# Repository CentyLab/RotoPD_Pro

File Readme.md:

## RotoPD Pro - USB-C PD 3.1 Breakout I2C 240W

## Related Links
- [AP33772S Arduino - GitHub](https://github.com/CentyLab/AP33772S-CentyLab)
- [INA238 Arduino - GitHub](https://github.com/RobTillaart/INA238)
- [RotoPD Pro Project - Hackaday](https://hackaday.io/project/204943-rotopd-pro-usb-c-240w-breakout-i2c)

You can install the libraries directly on ArduinoIDE. Library version 1.1.0 and later will support RotoPD Pro

## Description

While traditional power adapters can provide a variety of current but fixed to 5V output, our RotoPD Pro leverages advanced power delivery protocols to achieve a versatile output range — 4.5V to 48V at 240W max. The breakout board use a stand alone Power Delivery Sink controller to negotiate with your modern charger and provide different output voltage.

Centylab's RotoPD Pro can unlock more advance mode in your USB-C power supplies like Programmable Power Supply (PPS) and Adjustable Voltage Supply (AVS), to provide even more granular voltage adjustment. The RotoPD Pro simplifies power negotiation with USB-C adapters, handling the complex process of establishing power delivery contracts. The controller does all the heavy lifting of power negotiation and provides an easy way to configure over I2C, free your micro-controller from the complicated USB-C PD protocol.

To config the board, you will need an I2C bus. The board integrates seamlessly into the Qwiic and STEMMA QT ecosystems, no soldering is required. Unlike the previous version, the board only work with **3.3V I2C logic voltage.**

To make it even easier to use, RotoPD Pro includes a built-in buck converter that efficiently steps down USB-C VBUS power to a stable 5V output, making it perfect for powering microcontrollers, sensors, and other low-voltage components in your project.

## Requirements for AVS
To ultilize AVS power profile, you will need a powerbank or charger that has AVS profile and a 240W USB-C cable. Here are some chargers that we found support AVS profile.

+ [Framework 180W](https://frame.work/products/16-power-adapter)

+ [Framework 240W](https://frame.work/products/power-adapter-240w)

+ [AMEGAT Powerbank 140W](https://www.amazon.com/AMEGAT-27600mAh-Portable-Recharge-Compatible/dp/B0CC2CGD3L)

+ [Baseus Powerbank 140W](https://www.amazon.com/Baseus-Portable-Charger-24000mAh-Charging/dp/B0CH8D2YHZ)

+ [UGREEEN Nexode 300W](https://www.amazon.com/UGREEN-Charger-Charging-Station-Compatible/dp/B0DBZY57ZF)

## Specification
+ Input and output voltage range of  48V at 5A max
+ On board buck for 5V output at 1A max, 0.4A continuous
+ Support Qwiic or STEMMA QT connector with 3.3V logic
+ Support PD3.1 EPR/AVS Up to 48V and SPR/PPS Up to 21V
+ Certified USB PD3.1 v1.6  TID: 10062
+ Integrated ESD and flyback diode protection
+ Integrated NTC temperature monitoring
+ On board VBUS switch (back-to-back NMOS)
+ Current sensing from 0 to 5 A at ±2% accuracy up to 60C

## Pinout

## Schematic

## Demo
AVSCycle example with Sparkfun Pro Micro ESP32-C3. We are requesting AVS profile from 15V to 48V.

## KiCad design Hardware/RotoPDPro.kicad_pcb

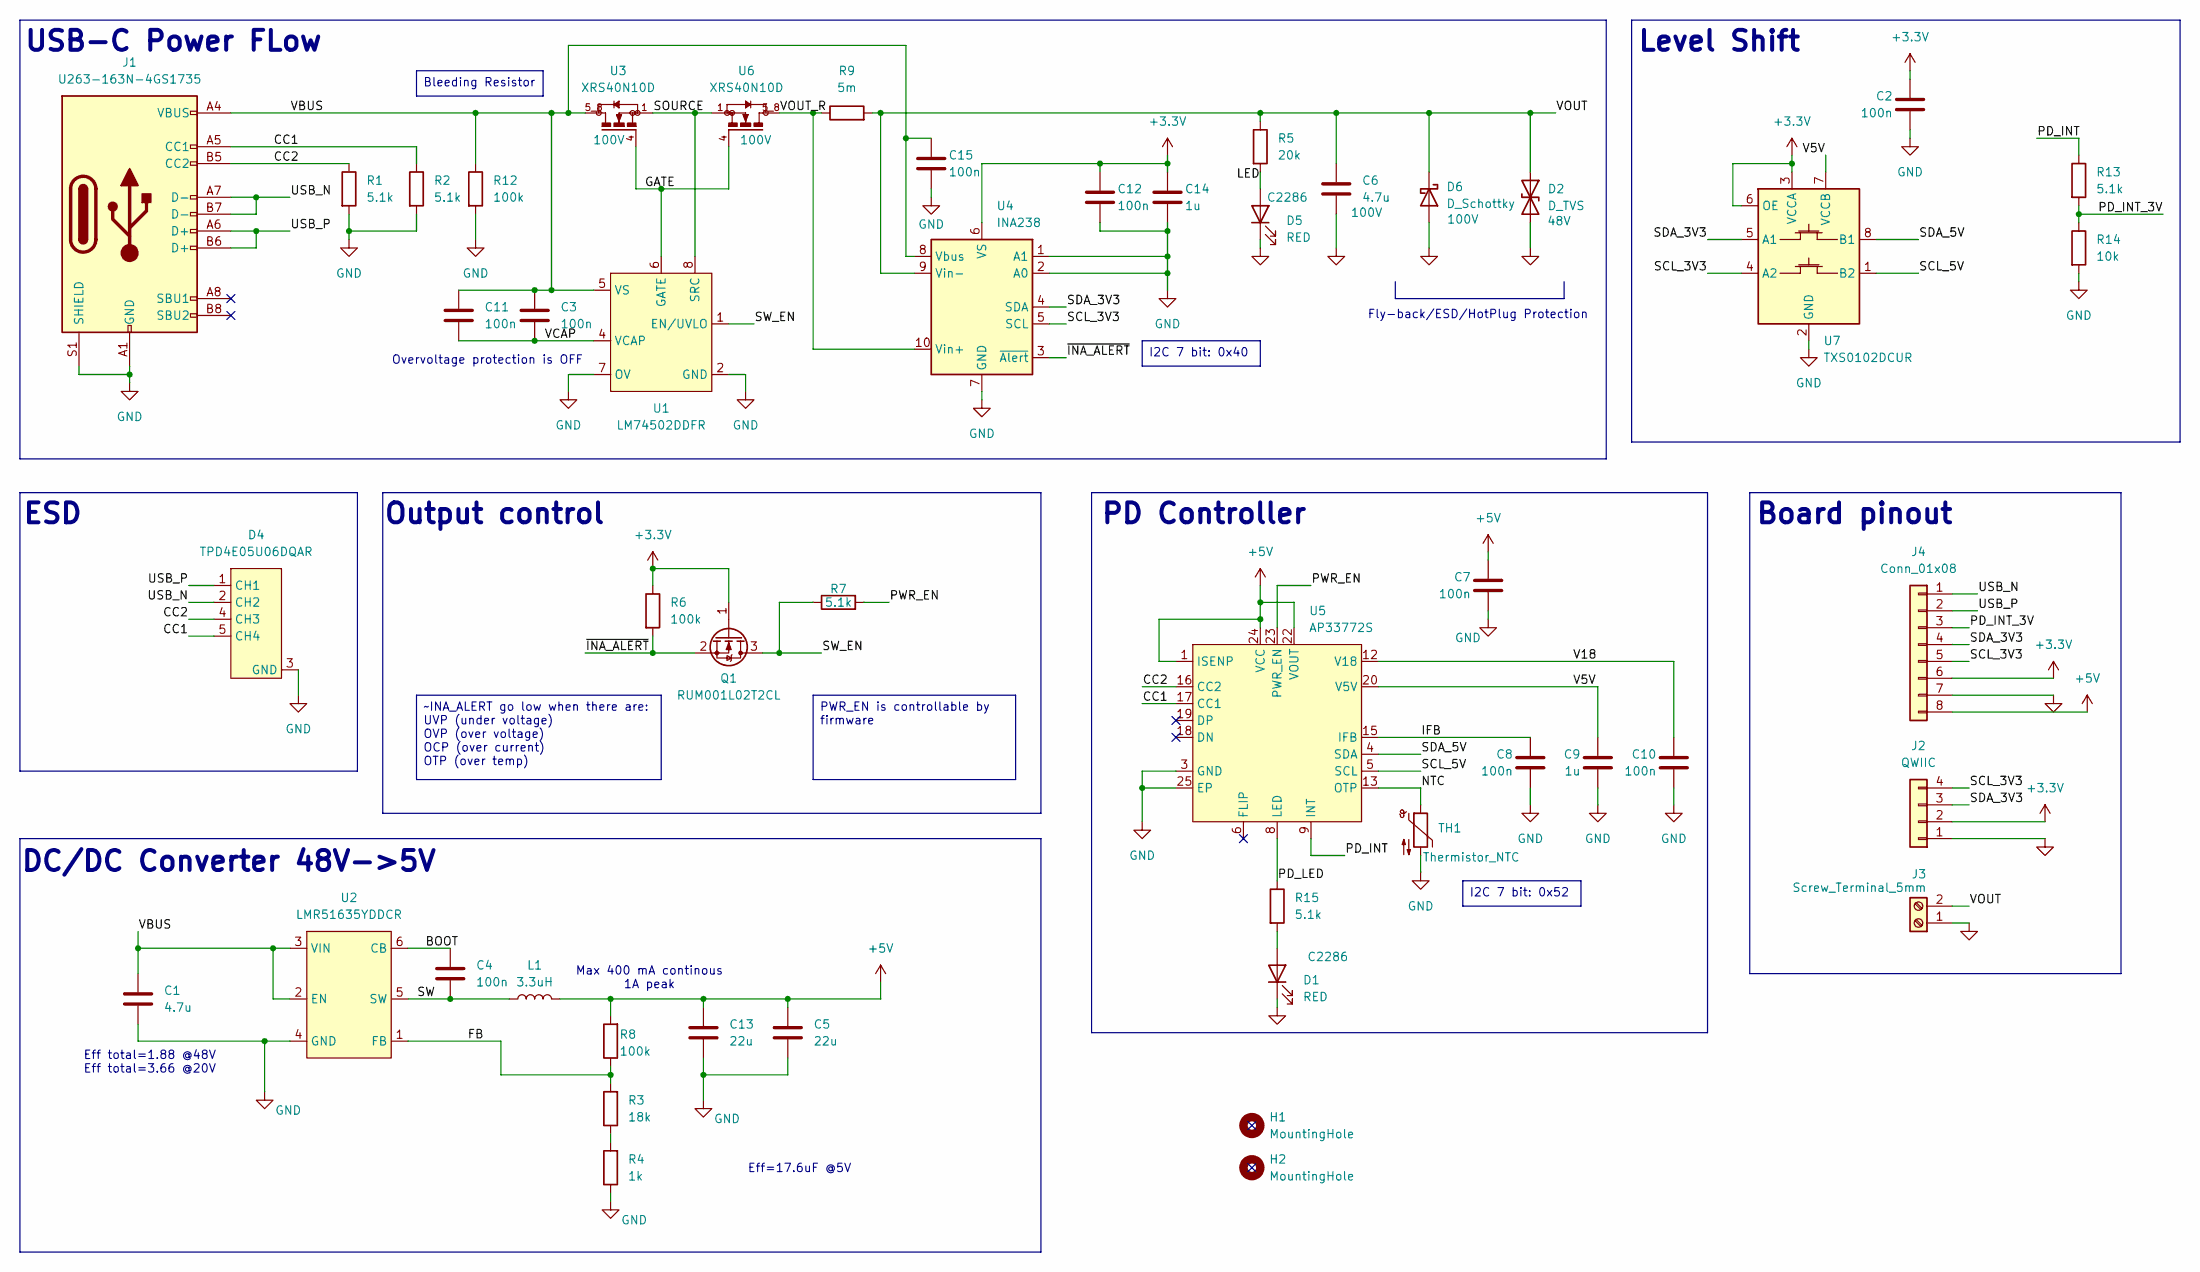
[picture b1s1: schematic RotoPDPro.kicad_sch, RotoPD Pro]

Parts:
C1: 4.7u; C_1210_3225Metric; LCSC C697607
C2, C3, C7, C8, C10, C11, C12, C15: 100n; C_0402_1005Metric; LCSC C162179
C4: 100n; R_0402_1005Metric; LCSC C162179
C5, C13: 22u; C_1210_3225Metric; LCSC C52306
C6: 4.7u; C_1210_3225Metric; Voltage 100V; LCSC C697607
C9, C14: 1u; C_0603_1608Metric; LCSC C15849
D1, D5: RED; LED_0603_1608Metric; LCSC C2286
D2: D_TVS; D_SOD-123F; Operating Voltage 48V; LCSC C2994213
D4: TPD4E05U06DQAR; SON50P100X255X50-10N; LCSC C138714
D6: D_Schottky; D_SOD-123; Voltage 100V; LCSC C908227
H1, H2: MountingHole; MountingHole_2.7mm_M2.5_DIN965_Pad_TopBottom
J1: U263-163N-4GS1735; USB_C_GSwitch; LCSC C2931470
J2: QWIIC; JST_SH_SM04B-SRSS-TB_1x04-1MP_P1.00mm_Horizontal; LCSC C160404
J3: Screw_Terminal_5mm; TerminalBlock_Phoenix_MKDS-1,5-2_1x02_P5.00mm_Horizontal
J4: Conn_01x08; PinHeader_1x08_P2.54mm_Vertical
L1: 3.3uH; L_APV_APH0530; LCSC C5349682
Q1: RUM001L02T2CL; SOT-723; LCSC C253528
R1, R2, R7, R13, R15: 5.1k; R_0402_1005Metric; LCSC C25905
R3: 18k; R_0603_1608Metric; LCSC C25810
R4: 1k; R_0402_1005Metric; LCSC C11702
R5: 20k; R_0603_1608Metric; LCSC C4184
R6, R8: 100k; R_0402_1005Metric; LCSC C25741
R9: 5m; R_0805_2012Metric; LCSC C22450690
R12: 100k; R_0603_1608Metric; LCSC C25803
R14: 10k; R_0402_1005Metric; LCSC C25744
TH1: Thermistor_NTC; R_0402_1005Metric; LCSC C77131
U1: LM74502DDFR; TSOT-23-8; LCSC C5219202
U2: LMR51635YDDCR; TSOT-23-6; LCSC Part C45262770
U3, U6: XRS40N10D; DFN-8(3.3x3.3); Voltage 100V; LCSC C50314150
U4: INA238; VSSOP-10_3x3mm_P0.5mm; LCSC C2868250
U5: AP33772S; QFN-24-1EP_4x4mm_P0.5mm_EP2.6x2.6mm; LCSC C24374260
U7: TXS0102DCUR; VSSOP-8_2.3x2mm_P0.5mm; LCSC C53434

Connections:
+3.3V: C2.1, C12.1, C14.1, J2.2, J4.6, Q1.1 (G), R6.1, U4.6 (VS), U7.3 (VCCA), U7.6 (OE)
+5V: C5.1, C7.1, C13.1, J4.8, L1.2, R8.2, U5.1 (ISENP), U5.22 (VOUT), U5.24 (VCC)
/BOOT: C4.2, U2.6 (CB)
/CC1: D4.5 (CH4), D4.6, J1.A5 (CC1), R2.1, U5.17 (CC1)
/CC2: D4.4 (CH3), D4.7, J1.B5 (CC2), R1.1, U5.16 (CC2)
/FB: R3.2, R8.1, U2.1 (FB)
/GATE: U1.6 (GATE), U3.4, U6.4
/IFB: C8.1, U5.15 (IFB)
/LED: D5.2 (A), R5.2
/NTC: TH1.1, U5.13 (OTP)
/PD_INT: R13.1, U5.9 (INT)
/PD_INT_3V: J4.3, R13.2, R14.1
/PD_LED: R15.1, U5.8 (LED)
/PWR_EN: R7.2, U5.23 (PWR_EN)
/SCL_3V3: J2.4, J4.5, U4.5 (SCL), U7.4 (A2)
/SCL_5V: U5.5 (SCL), U7.1 (B2)
/SDA_3V3: J2.3, J4.4, U4.4 (SDA), U7.5 (A1)
/SDA_5V: U5.4 (SDA), U7.8 (B1)
/SOURCE: U1.8 (SRC), U3.1, U3.2, U3.3, U6.1, U6.2, U6.3
/SW: C4.1, L1.1, U2.5 (SW)
/SW_EN: Q1.3 (D), R7.1, U1.1 (EN/UVLO)
/USB_N: D4.2 (CH2), D4.9, J1.A7 (D-), J1.B7 (D-), J4.1
/USB_P: D4.1 (CH1), D4.10, J1.A6 (D+), J1.B6 (D+), J4.2
/V5V: C9.1, U5.20 (V5V), U7.7 (VCCB)
/V18: C10.1, U5.12 (V18)
/VBUS: C1.1, C3.2, C11.2, C15.1, J1.A4 (VBUS), J1.A9 (VBUS), J1.B4 (VBUS), J1.B9 (VBUS), R12.1, U1.5 (VS), U2.2 (EN), U2.3 (VIN), U3.5_8, U4.8 (Vbus)
/VCAP: C3.1, C11.1, U1.4 (VCAP)
/VOUT: C6.1, D2.1 (A1), D6.1 (K), J3.2, R5.1, R9.2, U4.9 (Vin-)
/VOUT_R: R9.1, U4.10 (Vin+), U6.5_8
/~INA_ALERT: Q1.2 (S), R6.2, U4.3 (~Alert)
GND: C1.2, C2.2, C5.2, C6.2, C7.2, C8.2, C9.2, C10.2, C12.2, C13.2, C14.2, C15.2, D1.1 (K), D2.2 (A2), D4.3 (GND), D4.8 (GND), D5.1 (K), D6.2 (A), J1.A1 (GND), J1.A12 (GND), J1.B1 (GND), J1.B12 (GND), J1.S1 (SHIELD), J2.1, J3.1, J4.7, R1.2, R2.2, R4.1, R12.2, R14.2, TH1.2, U1.2 (GND), U1.7 (OV), U2.4 (GND), U4.1 (A1), U4.2 (A0), U4.7 (GND), U5.3 (GND), U5.25 (EP), U7.2 (GND)
unnamed: D1.2 (A), R15.2
unnamed: R3.1, R4.2
unnamed: U5.2 (NC), U5.7 (NC), U5.10 (NC), U5.11 (NC), U5.14 (NC), U5.21 (NC)

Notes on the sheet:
Output control
Eff total=1.88 @48V Eff total=3.66 @20V
DC/DC Converter 48V->5V
ESD
Eff=17.6uF @5V
Max 400 mA continous 1A peak
Level Shift
Overvoltage protection is OFF
PD Controller
USB-C Power FLow
Fly-back/ESD/HotPlug Protection
Board pinout
~INA_ALERT go low when there are: UVP (under voltage) OVP (over voltage) OCP (over current) OTP (over temp)
I2C 7 bit: 0x40
Bleeding Resistor
I2C 7 bit: 0x52
PWR_EN is controllable by firmware

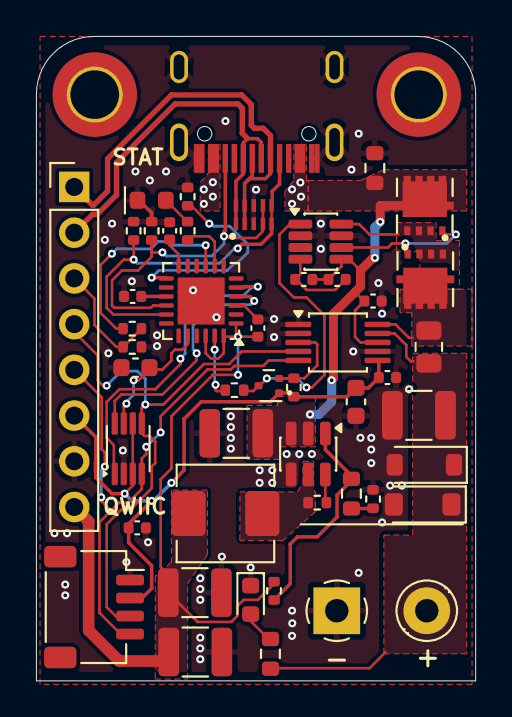
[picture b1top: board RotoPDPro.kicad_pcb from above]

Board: 2 copper layers, 24.4 x 35.8 mm, 49 parts (0 on the bottom side), 34 nets.

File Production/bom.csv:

Designator,Footprint,Quantity,Value,LCSC Part #
"C1, C6",1210,2,4.7u,C697607
"C10, C11, C12, C15, C2, C3, C4, C7, C8",402,9,100n,C162179
"C13, C5",1210,2,22u,C52306
"C14, C9",603,2,1u,C15849
"D1, D5",603,2,RED,C2286
D2,D_SOD-123F,1,D_TVS,C2994213
D4,SON50P100X255X50-10N,1,TPD4E05U06DQAR,C138714
D6,D_SOD-123,1,D_Schottky,C908227
J1,USB_C_XKB_240W,1,U263-163N-4GS1735,C2931470
J2,JST_SH_SM04B-SRSS-TB_1x04-1MP_P1.00mm_Horizontal,1,QWIIC,C160404
J3,"TerminalBlock_Phoenix_MKDS-1,5-2_1x02_P5.00mm_Horizontal",1,Screw_Terminal_5mm,
J4,PinHeader_1x08_P2.54mm_Vertical,1,Conn_01x08,
L1,L_APV_APH0530,1,3.3uH,C5349682
Q1,SOT-723,1,RUM001L02T2CL,C253528
"R1, R13, R15, R2, R7",402,5,5.1k,C25905
R12,603,1,100k,C25803
R14,402,1,10k,C25744
R3,603,1,18k,C25810
R4,402,1,1k,C11702
R5,603,1,10k,C4184
"R6, R8",402,2,100k,C25741
R9,805,1,5m,C22450690
TH1,402,1,Thermistor_NTC,C77131
U1,TSOT-23-8,1,LM74502DDFR,C5219202
U2,TSOT-23-6,1,LMR51635YDDCR,C45262770
"U3, U6",DFN-8(3.3x3.3),2,XRS40N10D,C50314150
U4,VSSOP-10_3x3mm_P0.5mm,1,INA238,C2868250
U5,QFN-24-1EP_4x4mm_P0.5mm_EP2.6x2.6mm,1,AP33772S,C24374260
U7,VSSOP-8_2.3x2mm_P0.5mm,1,TXS0102DCUR,C53434

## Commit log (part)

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2026-04-15 V1.1
2026-04-15 Update photo
